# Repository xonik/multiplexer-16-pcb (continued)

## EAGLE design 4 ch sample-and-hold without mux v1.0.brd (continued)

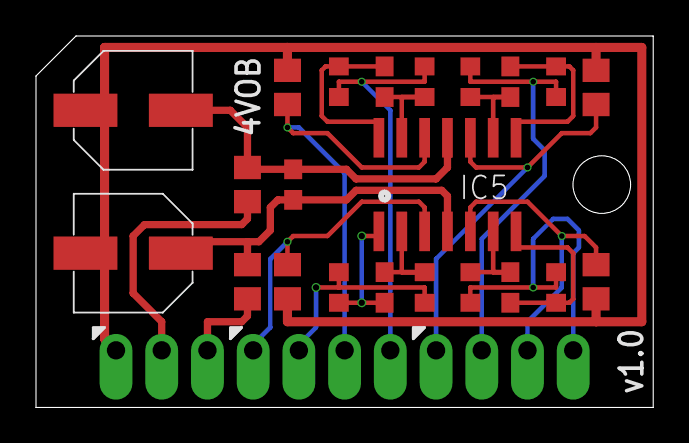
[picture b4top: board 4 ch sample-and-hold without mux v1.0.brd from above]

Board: 2 copper layers, 34.3 x 20.6 mm, 26 parts (1 on the bottom side), 21 nets.

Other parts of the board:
U$1: XONIK_LOGO_20

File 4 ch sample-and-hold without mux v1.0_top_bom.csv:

Comment,Designator,Footprint,LCSC Part #
0.1uF,C31 C36 C37 C38 C39,C0603,C14663
1k,R27 R29 R31 R33,R0603,C21190
10nF,C26 C27 C28 C29,C0805,C1710
22uF 25V,C2 C3,CAPAE660X610N,C134761
100R,R1 R2,R0805,C17408
100R,R28 R30 R32 R34,R0603,C22775
